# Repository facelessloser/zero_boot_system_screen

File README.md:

# zero_boot_system_screen
zero_boot_system_screen

Blog post - https://facelesstech.wordpress.com/2018/11/05/pi-boot-system/
Youtube - https://www.youtube.com/watch?v=CKD1gWXzSro

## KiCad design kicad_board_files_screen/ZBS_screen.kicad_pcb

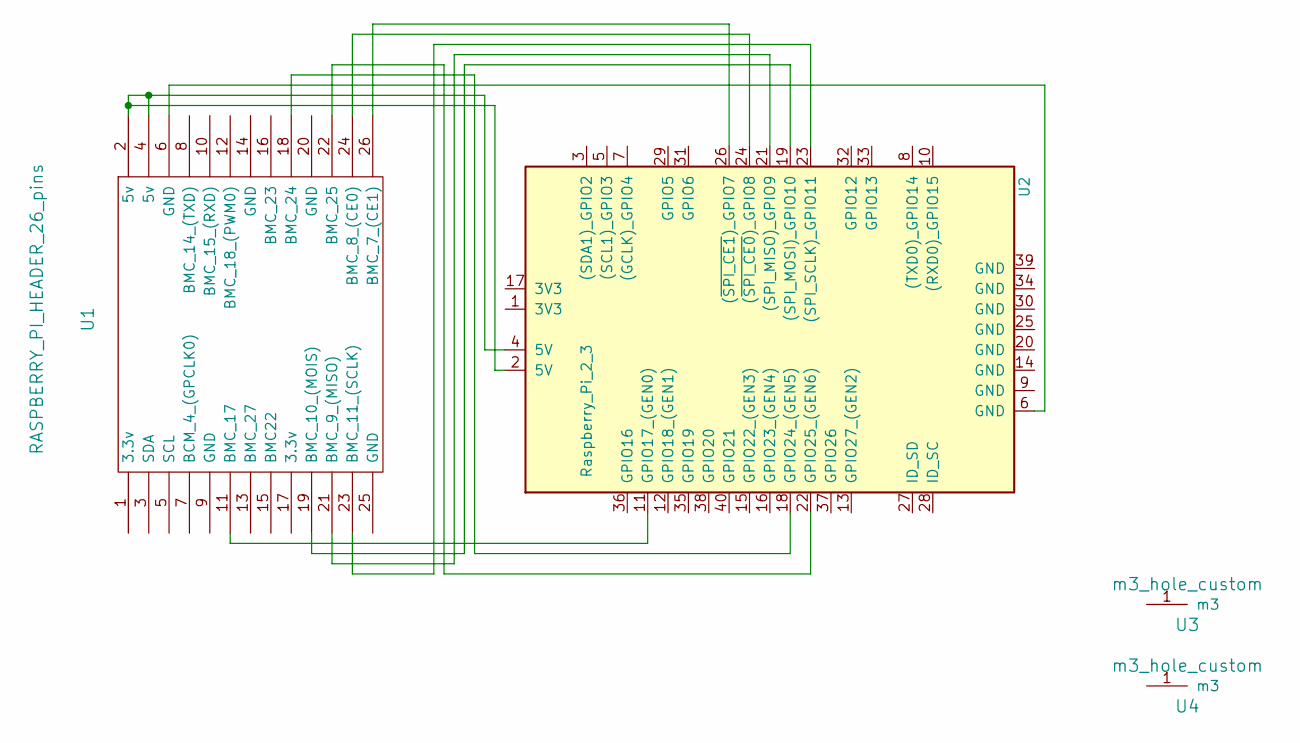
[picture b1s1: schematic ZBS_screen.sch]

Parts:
U1: RASPBERRY_PI_HEADER_26_pins; raspberry_pi_gpio_26pin_custom
U2: Raspberry_Pi_2_3; raspberry_pi_gpio_custom
U3, U4: m3_hole_custom

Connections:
unnamed: U1.2 (5v), U1.4 (5v), U2.2 (5V), U2.4 (5V)
unnamed: U1.6 (GND), U2.6 (GND)
unnamed: U1.11 (BMC_17), U2.11 (GPIO17_(GEN0))
unnamed: U1.18 (BMC_24), U2.18 (GPIO24_(GEN5))
unnamed: U1.19 (BMC_10_(MOIS)), U2.19 ((SPI_MOSI)_GPIO10)
unnamed: U1.21 (BMC_9_(MISO)), U2.21 ((SPI_MISO)_GPIO9)
unnamed: U1.22 (BMC_25), U2.22 (GPIO25_(GEN6))
unnamed: U1.23 (BMC_11_(SCLK)), U2.23 ((SPI_SCLK)_GPIO11)
unnamed: U1.24 (BMC_8_(CE0)), U2.24 ((~SPI_CE0~)_GPIO8)
unnamed: U1.26 (BMC_7_(CE1)), U2.26 ((~SPI_CE1~)_GPIO7)

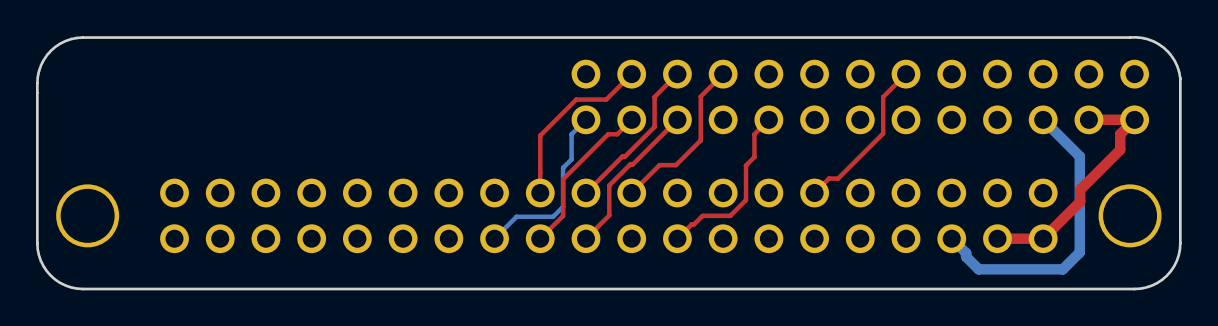
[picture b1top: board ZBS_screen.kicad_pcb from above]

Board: 2 copper layers, 63.5 x 14.0 mm, 4 parts (0 on the bottom side), 10 nets.

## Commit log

2019-02-03 board files
2019-02-03 added links
